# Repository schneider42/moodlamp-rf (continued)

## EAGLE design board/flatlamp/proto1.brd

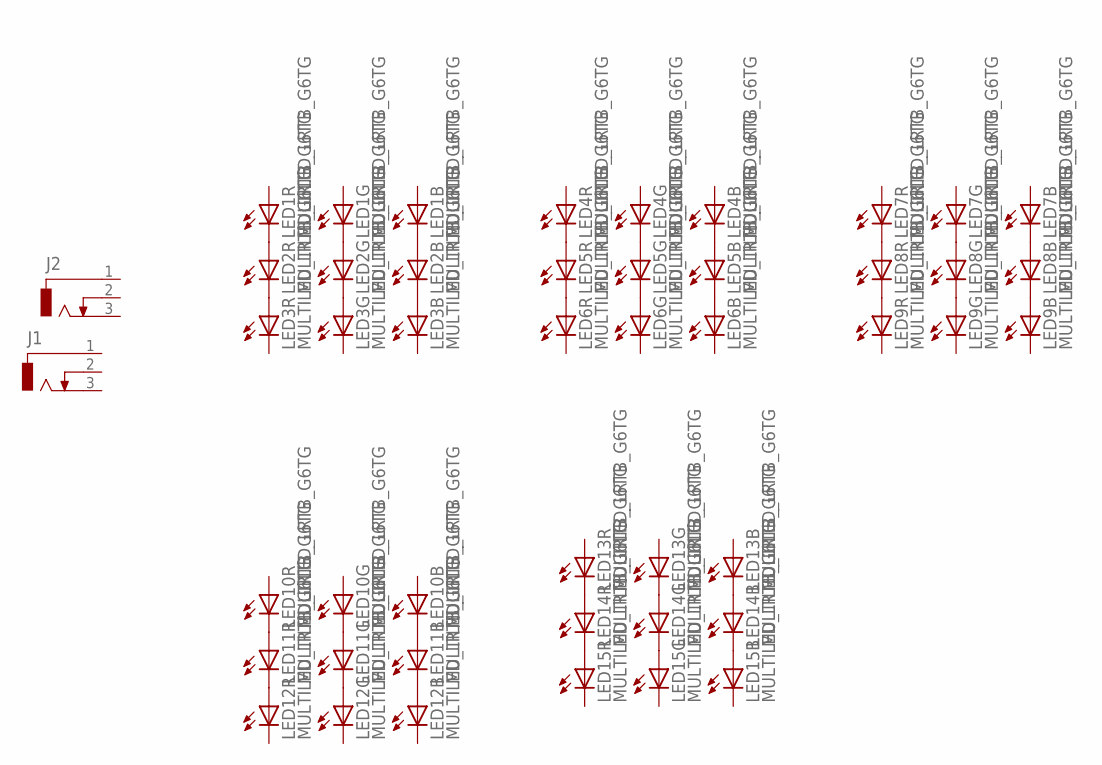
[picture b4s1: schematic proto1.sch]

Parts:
J1, J2: DCJ0303
LED1, LED2, LED3, LED4, LED5, LED6, LED7, LED8, LED9, LED10, LED11, LED12, LED13, LED14, LED15: MULTILED_LRTB_G6TG; P-LCC-6_TOPLED

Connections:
unnamed: LED1.C1 (C), LED2.A1 (A)
unnamed: LED1.C2 (C), LED2.A2 (A)
unnamed: LED1.C3 (C), LED2.A3 (A)
unnamed: LED2.C3 (C), LED3.A3 (A)
unnamed: LED2.C2 (C), LED3.A2 (A)
unnamed: LED2.C1 (C), LED3.A1 (A)
unnamed: LED4.C1 (C), LED5.A1 (A)
unnamed: LED4.C2 (C), LED5.A2 (A)
unnamed: LED4.C3 (C), LED5.A3 (A)
unnamed: LED5.C3 (C), LED6.A3 (A)
unnamed: LED5.C2 (C), LED6.A2 (A)
unnamed: LED5.C1 (C), LED6.A1 (A)
unnamed: LED7.C1 (C), LED8.A1 (A)
unnamed: LED7.C2 (C), LED8.A2 (A)
unnamed: LED7.C3 (C), LED8.A3 (A)
unnamed: LED8.C1 (C), LED9.A1 (A)
unnamed: LED8.C2 (C), LED9.A2 (A)
unnamed: LED8.C3 (C), LED9.A3 (A)
unnamed: LED11.C1 (C), LED12.A1 (A)
unnamed: LED10.C1 (C), LED11.A1 (A)
unnamed: LED10.C2 (C), LED11.A2 (A)
unnamed: LED11.C2 (C), LED12.A2 (A)
unnamed: LED10.C3 (C), LED11.A3 (A)
unnamed: LED11.C3 (C), LED12.A3 (A)
unnamed: LED13.C1 (C), LED14.A1 (A)
unnamed: LED13.C2 (C), LED14.A2 (A)
unnamed: LED13.C3 (C), LED14.A3 (A)
unnamed: LED14.C1 (C), LED15.A1 (A)
unnamed: LED14.C2 (C), LED15.A2 (A)
unnamed: LED14.C3 (C), LED15.A3 (A)

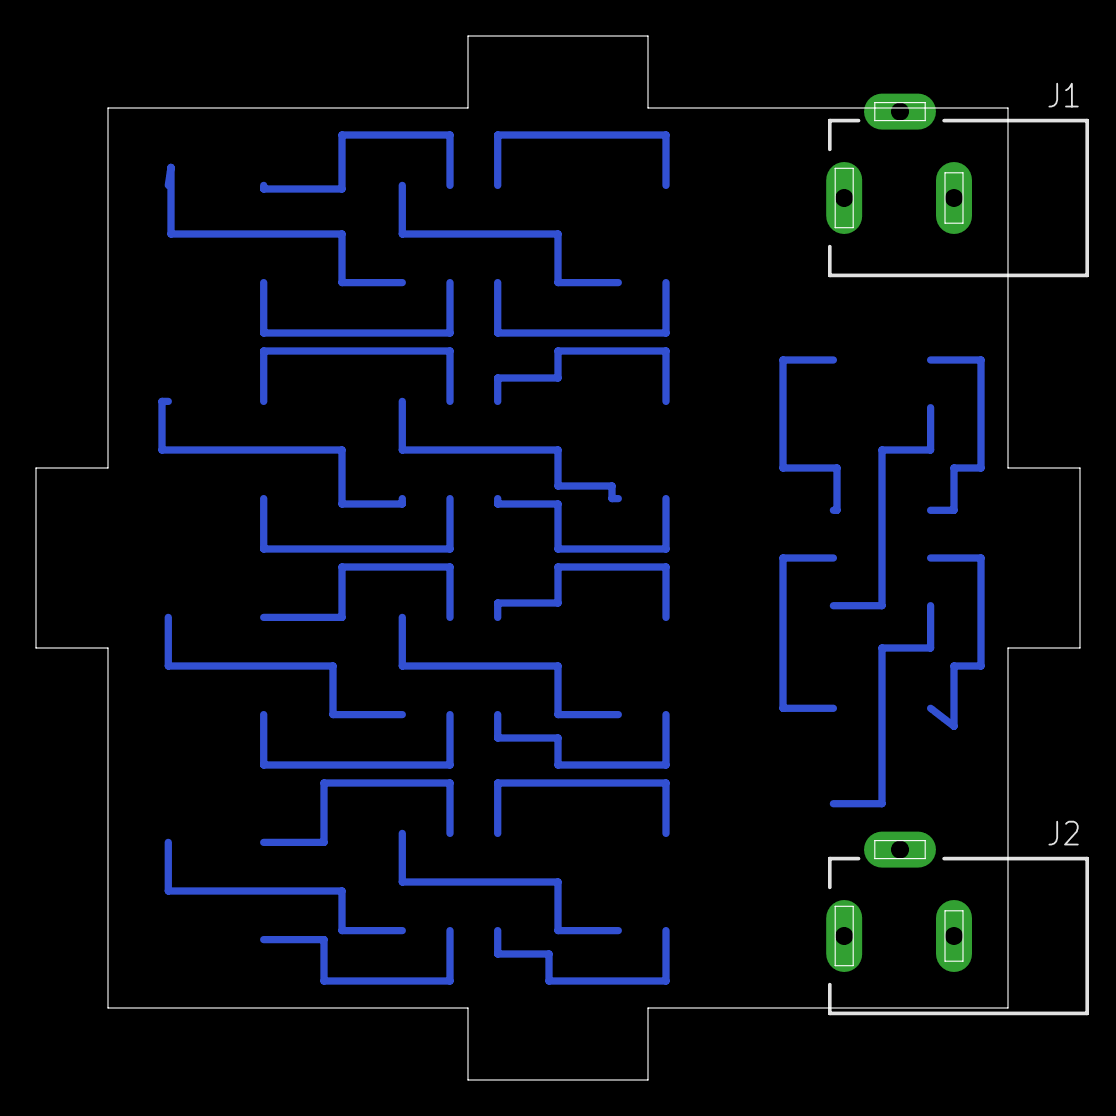
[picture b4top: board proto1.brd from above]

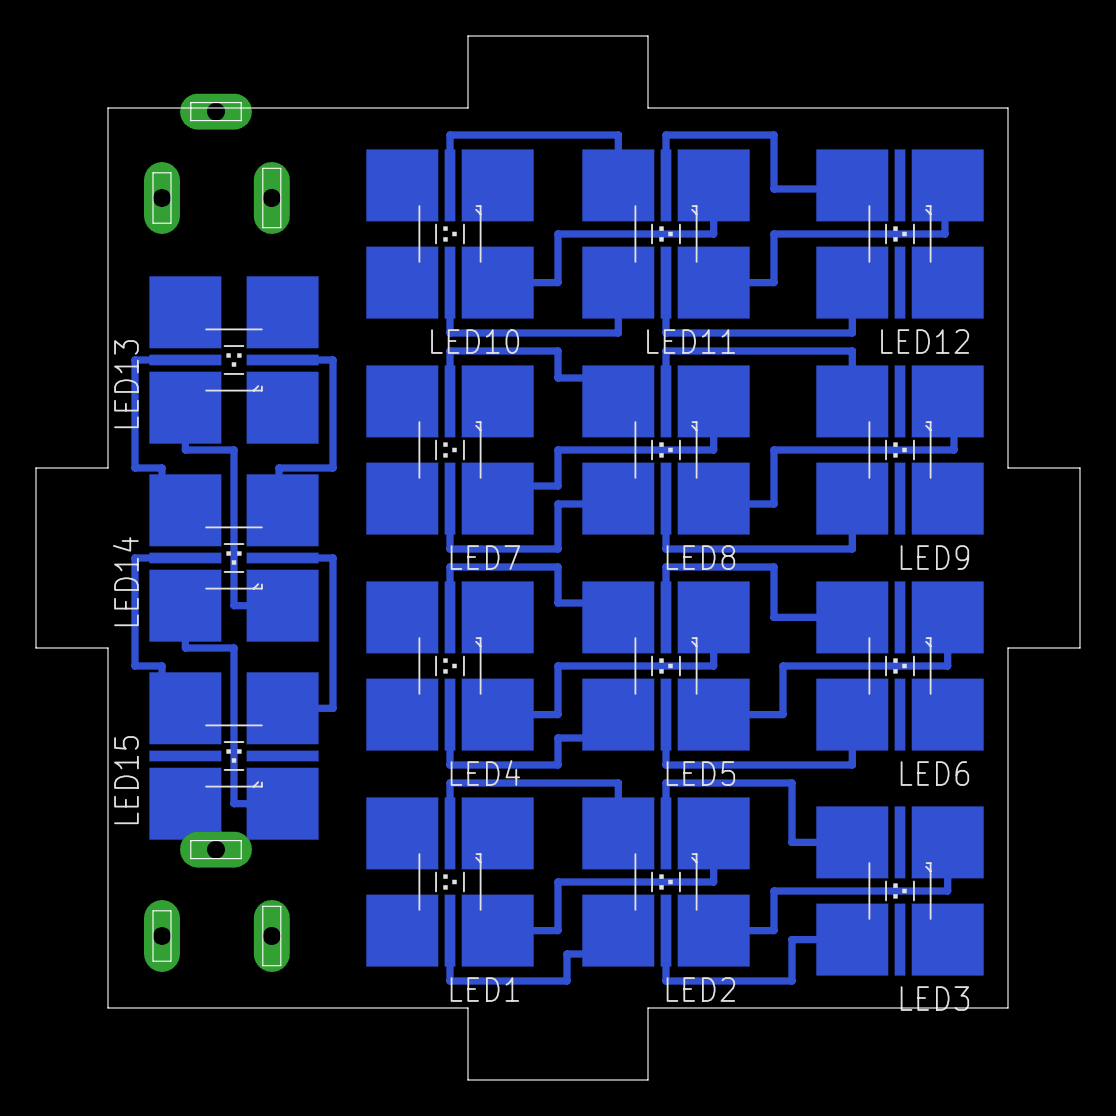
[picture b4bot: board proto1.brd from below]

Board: 2 copper layers, 58.0 x 58.0 mm, 17 parts (15 on the bottom side), 30 nets.

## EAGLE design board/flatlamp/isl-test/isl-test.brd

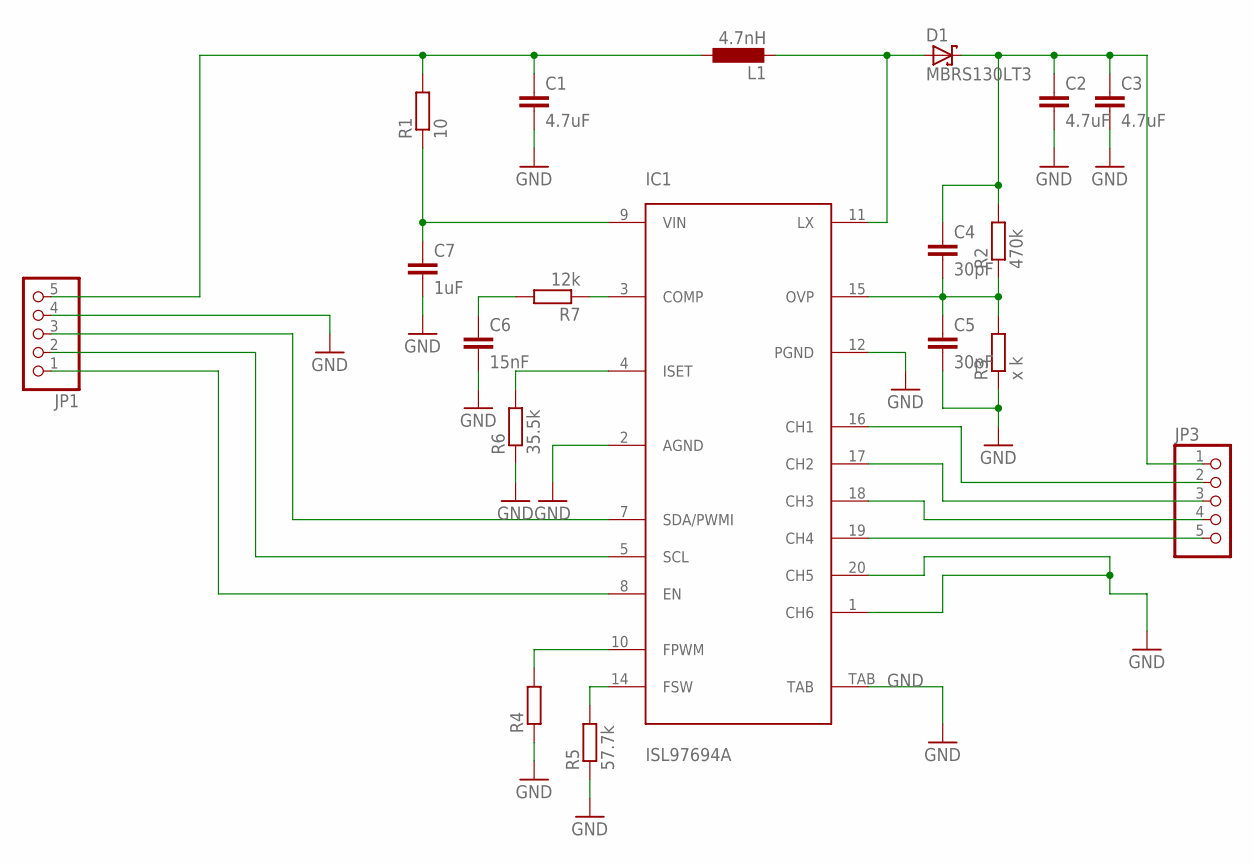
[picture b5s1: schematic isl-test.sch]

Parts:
C1, C2, C3: 4.7uF; C0805
C4, C5: 30pF; C0603
C6: 15nF; C0603
C7: 1uF; C0603
D1: MBRS130LT3; SMB
IC1: ISL97694A; TQFN-20
JP1, JP3: PINHD-1X5; 1X05
L1: 4.7nH; L1812
R1: 10; R0603
R2: 470k; R0603
R3: x k; R0603
R4: R-EU_R0603; R0603
R5: 57.7k; R0603
R6: 35.5k; R0603
R7: 12k; R0603

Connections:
GND: C1.2, C2.2, C3.2, C5.2, C6.2, C7.2, IC1.1 (CH6), IC1.2 (AGND), IC1.12 (PGND), IC1.20 (CH5), IC1.TAB, JP1.4, R3.1, R4.1, R5.1, R6.1
unnamed: C1.1, JP1.5, L1.1, R1.2
unnamed: D1.A, IC1.11 (LX), L1.2
unnamed: C4.2, C5.1, IC1.15 (OVP), R2.1, R3.2
unnamed: C2.1, C3.1, C4.1, D1.C, JP3.1, R2.2
unnamed: IC1.3 (COMP), R7.1
unnamed: C6.1, R7.2
unnamed: IC1.4 (ISET), R6.2
unnamed: IC1.10 (FPWM), R4.2
unnamed: IC1.14 (FSW), R5.2
unnamed: IC1.8 (EN), JP1.1
unnamed: IC1.5 (SCL), JP1.2
unnamed: IC1.7 (SDA/PWMI), JP1.3
unnamed: IC1.16 (CH1), JP3.2
unnamed: IC1.17 (CH2), JP3.3
unnamed: IC1.18 (CH3), JP3.4
unnamed: IC1.19 (CH4), JP3.5
VIN: C7.1, IC1.9 (VIN), R1.1

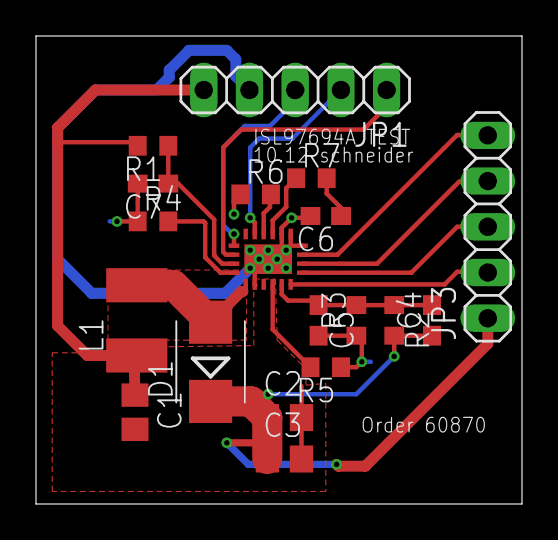
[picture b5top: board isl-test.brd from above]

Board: 2 copper layers, 27.0 x 26.0 mm, 19 parts (0 on the bottom side), 18 nets.

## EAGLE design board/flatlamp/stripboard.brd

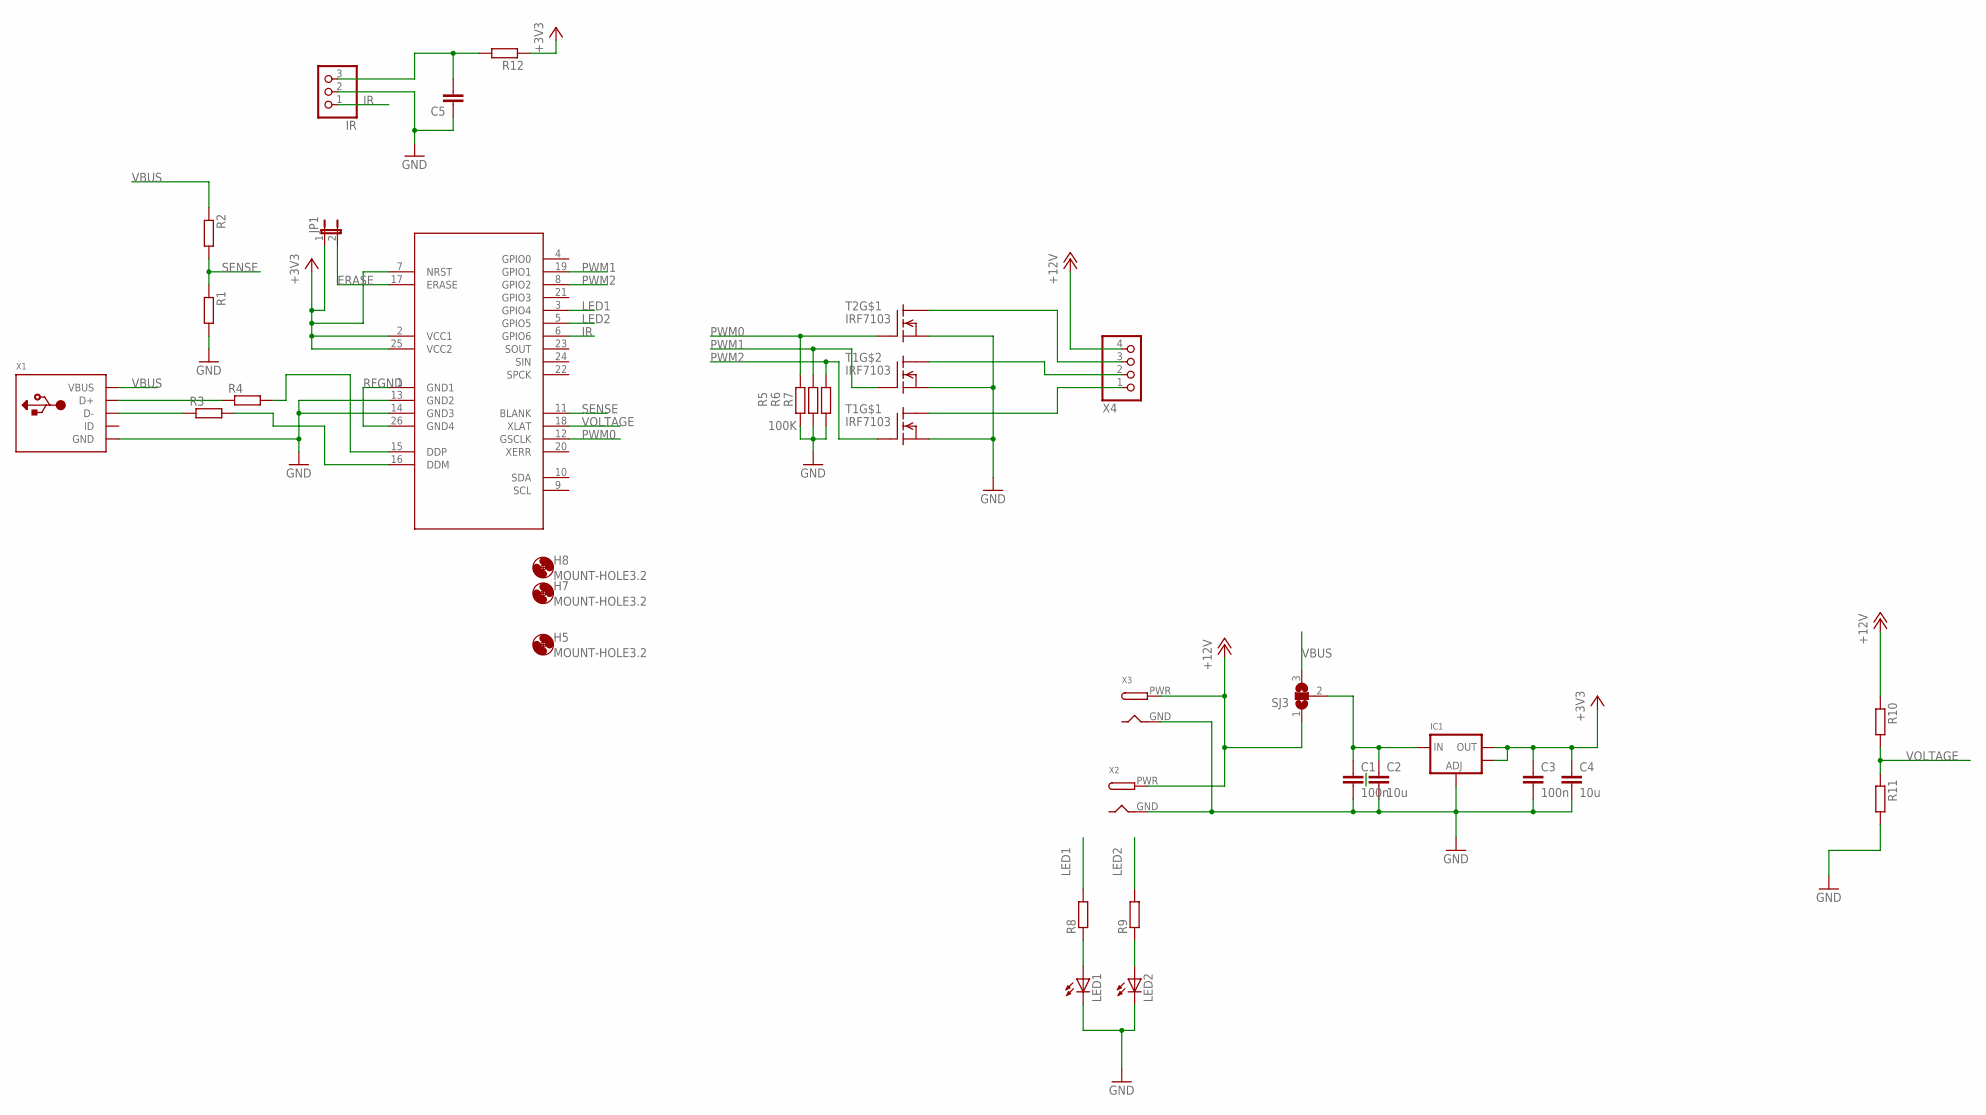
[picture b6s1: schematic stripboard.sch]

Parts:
C1, C3: 100n; C0805
C2, C4: 10u; C0805
C5: C-EUC0805; C0805
H5, H7, H8: MOUNT-HOLE3.2; 3,2
IC1: LM1117SOT223-REFLOW; SOT223-R
IR: PINHD-1X3; 1X03
JP1: JP1E; JP1
LED1, LED2: LEDCHIP-LED0805; CHIP-LED0805
R1, R2, R3, R4, R8, R9, R10, R11, R12: R-EU_R0805; R0805
R5, R6, R7: 100K; M0805
SJ3: SJ2W; SJ_2
T1, T2: IRF7103; SO-8
U$1: RFBOARD
X1: USBMINIB; USB-MINIB
X2, X3: DCBARRELPTH; DCJACK_2MM_PTH
X4: PINHD-1X4/90; 1X04/90

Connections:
+3V3: C3.1, C4.1, IC1.2 (OUT), IC1.4 (OUT1), JP1.1, R12.1, U$1.2 (VCC1), U$1.7 (NRST), U$1.25 (VCC2)
+12V: R10.1, SJ3.1, X2.PWR, X3.PWR, X4.4
ERASE: JP1.2, U$1.17 (ERASE)
GND: C1.2, C2.2, C3.2, C4.2, C5.1, IC1.1 (ADJ), IR.2, LED1.C, LED2.C, R1.2, R5.2, R6.2, R7.2, R11.2, T1.1 (S), T1.3 (S), T2.1 (S), U$1.13 (GND2), U$1.14 (GND3), X1.GND, X2.GND, X3.GND
IR: IR.1, U$1.6 (GPIO6)
LED1: R8.2, U$1.3 (GPIO4)
LED2: R9.2, U$1.5 (GPIO5)
unnamed: T1.8 (D1), X4.1
unnamed: T1.5 (D1), X4.2
unnamed: T2.8 (D1), X4.3
unnamed: LED1.A, R8.1
unnamed: LED2.A, R9.1
unnamed: R3.2, U$1.16 (DDM)
unnamed: R4.2, U$1.15 (DDP)
unnamed: R4.1, X1.D+
unnamed: C1.1, C2.1, IC1.3 (IN), SJ3.2
unnamed: R3.1, X1.D-
unnamed: C5.2, IR.3, R12.2
PWM0: R5.1, T2.2 (G), U$1.12 (GSCLK)
PWM1: R6.1, T1.4 (G), U$1.19 (GPIO1)
PWM2: R7.1, T1.2 (G), U$1.8 (GPIO2)
RFGND: U$1.1 (GND1), U$1.26 (GND4)
SENSE: R1.1, R2.2, U$1.11 (BLANK)
VBUS: R2.1, SJ3.3, X1.VBUS
VOLTAGE: R10.2, R11.1, U$1.18 (XLAT)

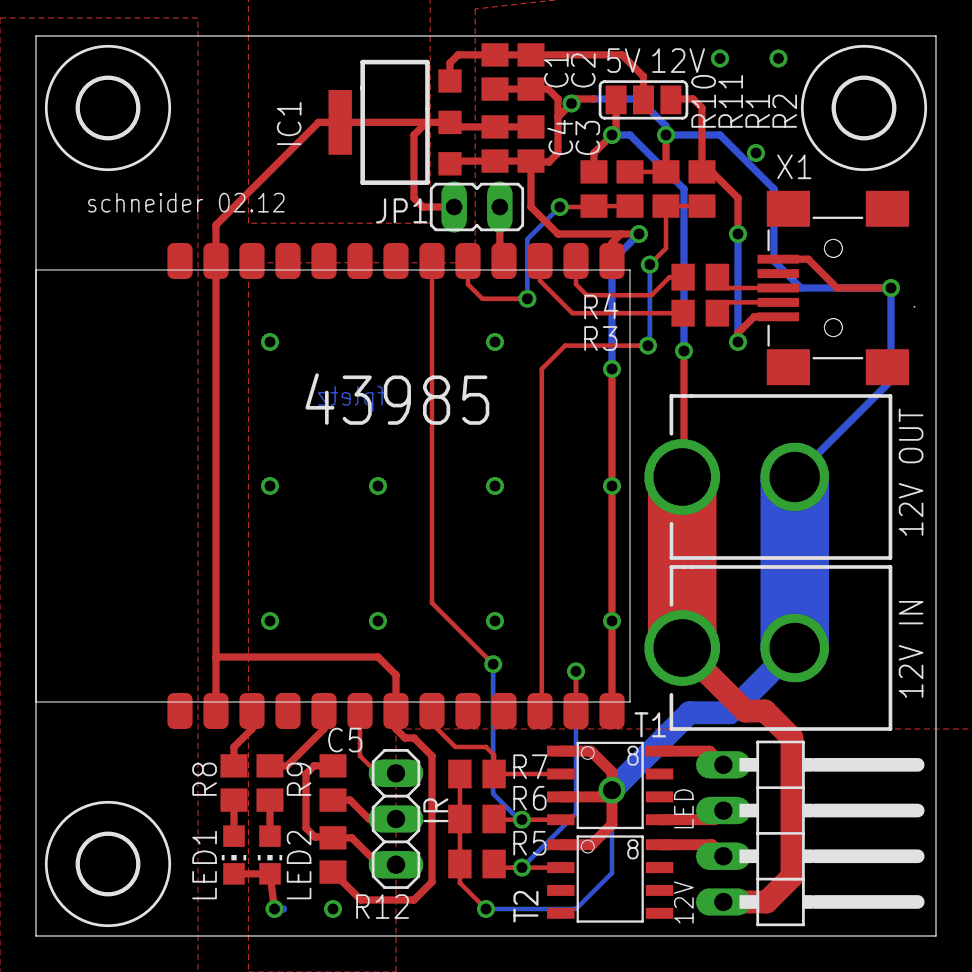
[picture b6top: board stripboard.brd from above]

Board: 2 copper layers, 50.0 x 50.0 mm, 33 parts (0 on the bottom side), 25 nets.

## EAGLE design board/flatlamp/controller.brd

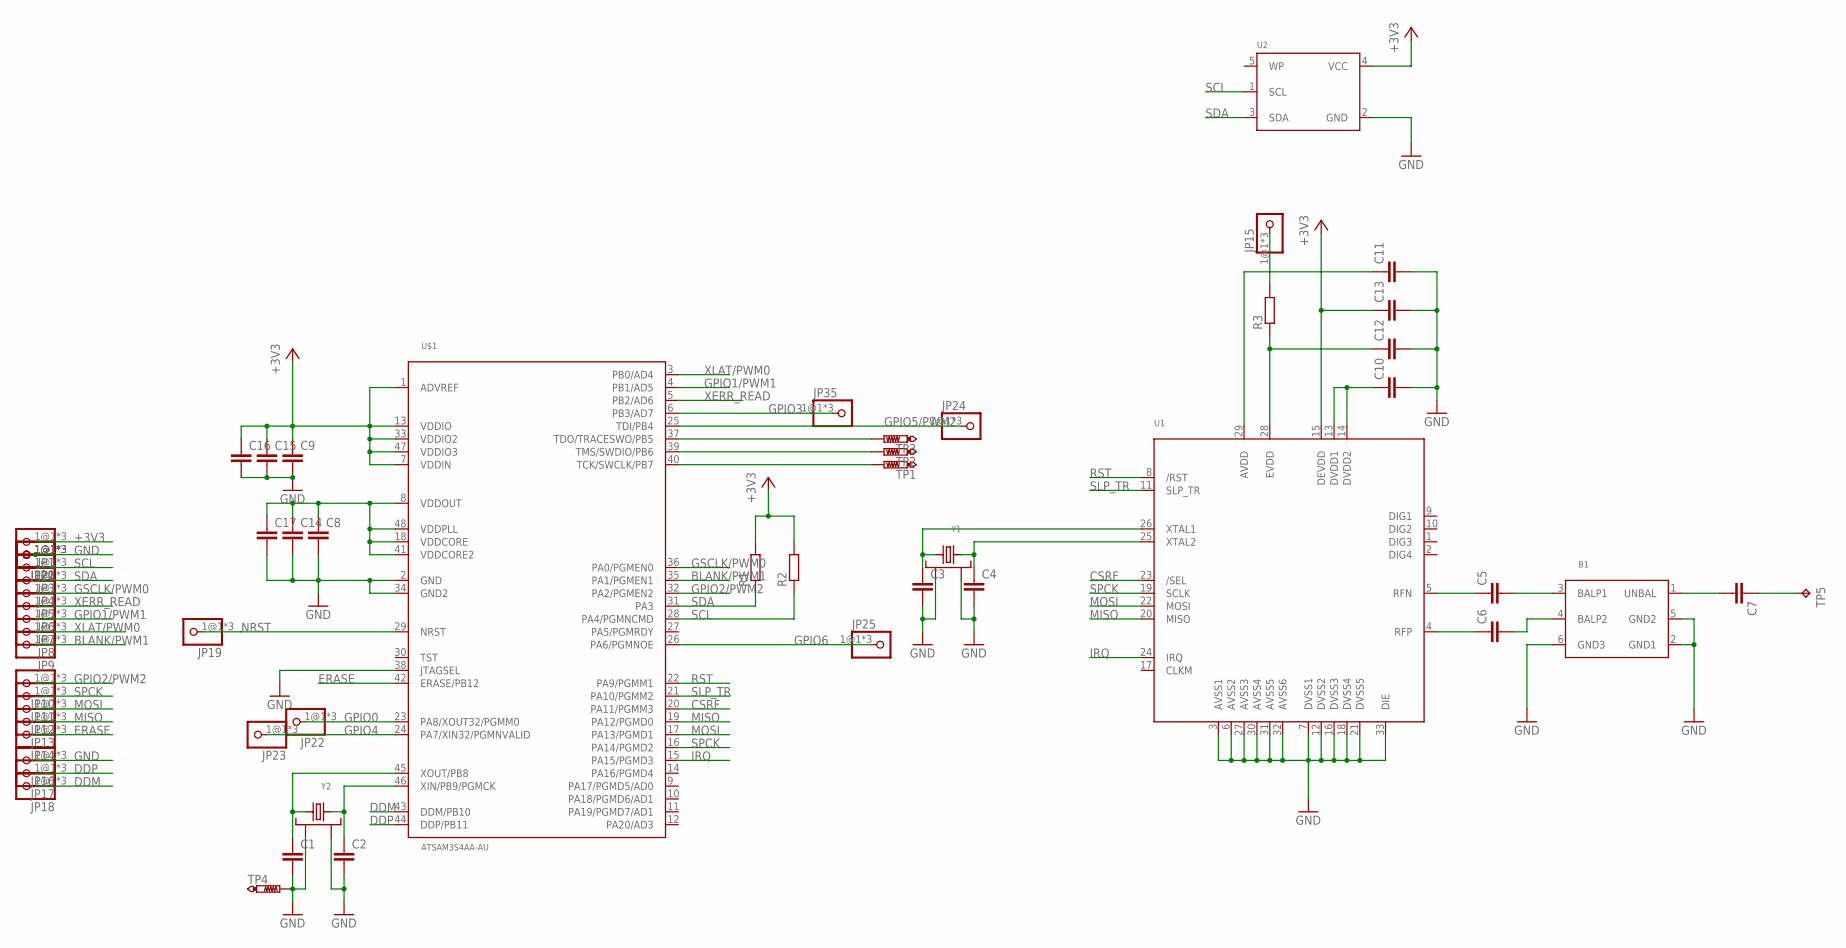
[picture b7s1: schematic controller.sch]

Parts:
B1: BALUN+LP; BALUN0805
C1, C2, C3, C4, C5, C6, C7: C-EUC0402K; C0402K
C8, C9, C10, C11, C12, C13, C14, C15, C16: C-EUC0603K; C0603K
C17: C-EUC0805K; C0805K
JP1, JP2, JP3, JP4, JP5, JP6, JP7, JP8, JP9, JP10, JP11, JP12, JP13, JP14, JP15, JP16, JP17, JP18, JP19, JP20, JP21, JP22, JP23, JP24, JP25, JP35: HEADER-1X1PAD; 1MMPAD
R1, R2: R-EU_R0402; R0402
R3: R-EU_R0805; R0805
TP1, TP2, TP3, TP4: PTR1TP15R; TP15R
TP5: TPTP15SQ; TP15SQ
U1: AT86RF212; 32QN2
U2: MCP24AA32; SOT23-5
U$1: ATSAM3S4AA-AU; LQFP48
Y1, Y2: CRYSTALTHIN; CRYSTAL_3.2X2.5

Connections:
+3V3: C9.1, C13.1, C15.1, C16.1, JP1.1@1, JP1.1@2, JP1.1@3, R1.2, R2.2, U1.15 (DEVDD), U2.4 (VCC), U$1.1 (ADVREF), U$1.7 (VDDIN), U$1.13 (VDDIO), U$1.33 (VDDIO2), U$1.47 (VDDIO3)
ANT: C7.1, TP5.TP
BLANK/PWM1: JP9.1@1, JP9.1@2, JP9.1@3, U$1.35 (PA1/PGMEN1)
CSRF: U1.23 (/SEL), U$1.20 (PA11/PGMM3)
DDM: JP18.1@1, JP18.1@2, JP18.1@3, U$1.43 (DDM/PB10)
DDP: JP17.1@1, JP17.1@2, JP17.1@3, U$1.44 (DDP/PB11)
ERASE: JP14.1@1, JP14.1@2, JP14.1@3, U$1.42 (ERASE/PB12)
GND: B1.2 (GND1), B1.5 (GND2), B1.6 (GND3), C1.2, C2.2, C3.2, C4.2, C8.2, C9.2, C10.2, C11.2, C12.2, C13.2, C14.2, C15.2, C16.2, C17.2, JP2.1@1, JP2.1@2, JP2.1@3, JP16.1@1, JP16.1@2, JP16.1@3, JP20.1@1, JP20.1@2, JP20.1@3, JP21.1@1, JP21.1@2, JP21.1@3, TP4.TP, U1.3 (AVSS1), U1.6 (AVSS2), U1.7 (DVSS1), U1.12 (DVSS2), U1.16 (DVSS3), U1.18 (DVSS4), U1.21 (DVSS5), U1.27 (AVSS3), U1.30 (AVSS4), U1.31 (AVSS5), U1.32 (AVSS6), U1.33 (DIE), U2.2 (GND), U$1.2 (GND), U$1.34 (GND2), U$1.38 (JTAGSEL), Y1.GND1, Y1.GND2, Y2.GND1, Y2.GND2
GPIO0: JP22.1@1, JP22.1@2, JP22.1@3, U$1.23 (PA8/XOUT32/PGMM0)
GPIO1/PWM1: JP7.1@1, JP7.1@2, JP7.1@3, U$1.4 (PB1/AD5)
GPIO2/PWM2: JP10.1@1, JP10.1@2, JP10.1@3, U$1.32 (PA2/PGMEN2)
GPIO3: JP35.1@1, JP35.1@2, JP35.1@3, U$1.6 (PB3/AD7)
GPIO4: JP23.1@1, JP23.1@2, JP23.1@3, U$1.24 (PA7/XIN32/PGMNVALID)
GPIO5/PWM2: JP24.1@1, JP24.1@2, JP24.1@3, U$1.25 (TDI/PB4)
GPIO6: JP25.1@1, JP25.1@2, JP25.1@3, U$1.26 (PA6/PGMNOE)
GSCLK/PWM0: JP5.1@1, JP5.1@2, JP5.1@3, U$1.36 (PA0/PGMEN0)
IRQ: U1.24 (IRQ), U$1.15 (PA15/PGMD3)
MISO: JP13.1@1, JP13.1@2, JP13.1@3, U1.20 (MISO), U$1.19 (PA12/PGMD0)
MOSI: JP12.1@1, JP12.1@2, JP12.1@3, U1.22 (MOSI), U$1.17 (PA13/PGMD1)
unnamed: C5.1, U1.5 (RFN)
unnamed: B1.3 (BALP1), C5.2
unnamed: C6.1, U1.4 (RFP)
unnamed: B1.4 (BALP2), C6.2
unnamed: C1.1, U$1.45 (XOUT/PB8), Y2.2
unnamed: C2.1, U$1.46 (XIN/PB9/PGMCK), Y2.1
unnamed: B1.1 (UNBAL), C7.2
unnamed: C3.1, U1.26 (XTAL1), Y1.2
unnamed: C4.1, U1.25 (XTAL2), Y1.1
unnamed: C12.1, R3.1, U1.28 (EVDD)
unnamed: C8.1, C14.1, C17.1, U$1.8 (VDDOUT), U$1.18 (VDDCORE), U$1.41 (VDDCORE2), U$1.48 (VDDPLL)
unnamed: C11.1, U1.29 (AVDD)
unnamed: JP15.1@1, JP15.1@2, JP15.1@3, R3.2
unnamed: C10.1, U1.13 (DVDD1), U1.14 (DVDD2)
unnamed: TP1.TP, U$1.40 (TCK/SWCLK/PB7)
unnamed: TP2.TP, U$1.39 (TMS/SWDIO/PB6)
unnamed: TP3.TP, U$1.37 (TDO/TRACESWO/PB5)
NRST: JP19.1@1, JP19.1@2, JP19.1@3, U$1.29 (NRST)
RST: U1.8 (/RST), U$1.22 (PA9/PGMM1)
SCL: JP3.1@1, JP3.1@2, JP3.1@3, R2.1, U2.1 (SCL), U$1.28 (PA4/PGMNCMD)
SDA: JP4.1@1, JP4.1@2, JP4.1@3, R1.1, U2.3 (SDA), U$1.31 (PA3)
SLP_TR: U1.11 (SLP_TR), U$1.21 (PA10/PGMM2)
SPCK: JP11.1@1, JP11.1@2, JP11.1@3, U1.19 (SCLK), U$1.16 (PA14/PGMD2)
XERR_READ: JP6.1@1, JP6.1@2, JP6.1@3, U$1.5 (PB2/AD6)
XLAT/PWM0: JP8.1@1, JP8.1@2, JP8.1@3, U$1.3 (PB0/AD4)

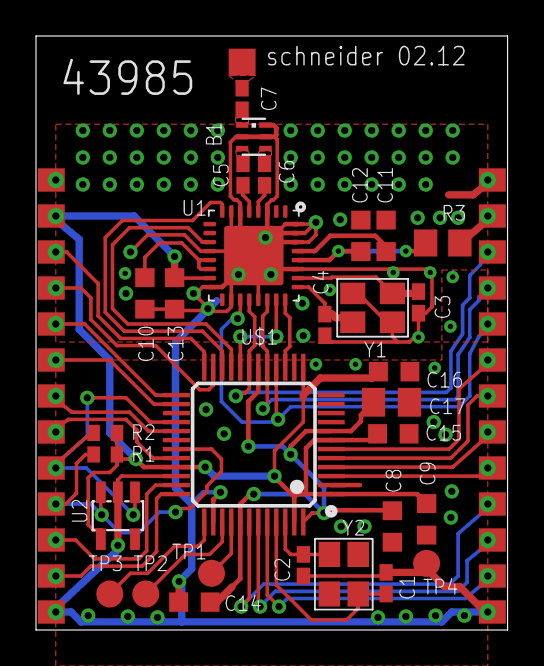
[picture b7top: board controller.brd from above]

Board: 2 copper layers, 26.2 x 33.0 mm, 57 parts (0 on the bottom side), 44 nets.

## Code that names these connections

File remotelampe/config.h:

/* vim:fdm=marker ts=4 et ai
 * {{{
 *         fnordlicht firmware next generation
 *
 *    for additional information please
 *    see http://koeln.ccc.de/prozesse/running/fnordlicht
 *
 * (c) by Alexander Neumann <alexander@bumpern.de>
 *     Lars Noschinski <lars@public.noschinski.de>
 *
 * This program is free software; you can redistribute it and/or modify
 * it under the terms of the GNU General Public License version 2 as
 * published by the Free Software Foundation.
 *
 * This program is distributed in the hope that it will be useful,
 * but WITHOUT ANY WARRANTY; without even the implied warranty of
 * MERCHANTABILITY or FITNESS FOR A PARTICULAR PURPOSE.  See the
 * GNU General Public License for more details.
 *
 * You should have received a copy of the GNU General Public License
 * along with this program; if not, write to the Free Software
 * Foundation, Inc., 675 Mass Ave, Cambridge, MA 02139, USA.
 *
 * For more information on the GPL, please go to:
 * http://www.gnu.org/copyleft/gpl.html
 }}} */

#ifndef _FNORDLICHT_CONFIG_H
#define _FNORDLICHT_CONFIG_H

#define BOARD_0_1       0       //old moodlamp design
#define BOARD_RF_0_1    1       //proto rf board
#define BOARD_RF_0_2    2       //current rf board

#ifndef BOARD
#define BOARD   BOARD_RF_0_2
#endif

#ifndef F_CPU
    #define F_CPU 18432000UL
#endif

#ifndef LED_PORT
#define LED_PORT PORTA
#endif

#ifndef LED_PORT_DDR
#define LED_PORT_DDR DDRA
#endif

#ifndef LED_PORT_INVERT
#define LED_PORT_INVERT 0
#endif

/* color <-> channel assignment */
#define CHANNEL_RED     0
#define CHANNEL_GREEN   1
#define CHANNEL_BLUE    2

#define RC5_DECODER 1
#define RS485_CTRL  1
#define SCRIPT_SPEED_CONTROL 1
#define STATIC_SCRIPTS 1
#define USB_CTRL 1
#define UART_BAUDRATE 230400
#define SERIAL_UART 1

#define CONFIG1_PIN     PB0
#define CONFIG1_PORT     B

#define JUMPER1C1_PIN     PC3
#define JUMPER1C1_PORT    C

#define JUMPER1C2_PIN     PC3
#define JUMPER1C2_PORT    C

#define LED3_PIN     PA4
#define LED3_PORT    A

#define LED2_PIN     PA5
#define LED2_PORT    A

#define LED1_PIN     PA7
#define LED1_PORT    A

#define xRC5C2_PORT     PORTB
#define	xRC5C2_IN       PINB
#define	xRC5C2          PB1			// IR input low active

#define xRC5C1_PORT     PORTD
#define	xRC5C1_IN       PIND
#define	xRC5C1          PD6			// IR input low active

#define ADC_MINBATIDLE  530         //4v

/* debug defines */
#ifndef DEBUG
#define DEBUG 0
#endif

/* include the script intpreter per default */
#ifndef STATIC_SCRIPTS
#define STATIC_SCRIPTS 1
#endif

/* include uart support per default */
#ifndef SERIAL_UART
#define SERIAL_UART 0
#endif

/* disable at keyboard decoder per default (EXPERIMENTAL) */
/* ATTENTION: THIS IS EXPERIMENTAL AND DOES NOT WORK ATM! */
#ifndef AT_KEYBOARD
#define AT_KEYBOARD 0
#endif

/* disable rc5-decoder per default */
#ifndef RC5_DECODER
#define RC5_DECODER 1
#endif

/* disable scripts speed control per default */
#ifndef SCRIPT_SPEED_CONTROL
#define SCRIPT_SPEED_CONTROL 1
#endif

/* fifo size must be a power of 2 and below 128 */
//#define UART_FIFO_SIZE 32
#ifndef UART_BAUDRATE
#define UART_BAUDRATE 19200
#endif

#ifndef PWM_USESCALE
#define PWM_USESCALE
#endif

/* enable this if you want to control a fnordlicht via RS485 */
#if RS485_CTRL

#define TEENSY_SUPPORT

#define RS485_TX_PIN_PORT   C
#define RS485_TX_PIN_PIN    PC4

#define RS485_NRX_PIN_PORT  C
#define RS485_NRX_PIN_PIN   PC5

#define ZBUS_BAUDRATE 115200
/*#define RS485_TX_DDR    DDRD
#define RS485_RX_DDR    DDRD
#define RS485_RX_PORT   PORTD
#define RS485_TX_PORT   PORTD

#define RS485_TX_PIN    PD4
#define RS485_NRX_PIN   PD5*/

#endif

/*#if (RS485_CTRL == 1) && (SERIAL_UART == 1) && !(ROLE == ROLE_MASTER)
#error "RS485_CTRL and SERIAL_UART are mutually exclusive!"
#endif*/


#include <avr/version.h>

/* check for avr-libc version */
#if __AVR_LIBC_VERSION__ < 10604UL
#error newer libc version (>= 1.6.4) needed!
#endif

/* check if cpu speed is defined */
#ifndef F_CPU
#error please define F_CPU!
#endif

/* check if this cpu is supported */
#if !(defined(__AVR_ATmega8__) || defined(__AVR_ATmega88__) || defined(__AVR_ATmega168__) || defined(__AVR_ATmega16__) || defined(__AVR_ATmega324P__)  || defined(__AVR_ATmega644P__) || defined(__AVR_ATmega32__))
#error "this cpu isn't supported yet!"
#endif

/* cpu specific configuration registers */
#if defined(__AVR_ATmega8__)
/* {{{ */
#define _ATMEGA8

#define _TIMSK_TIMER1 TIMSK
#define _UCSRB_UART0 UCSRB
#define _UDRIE_UART0 UDRIE
#define _TXEN_UART0 TXEN
#define _RXEN_UART0 RXEN
#define _RXCIE_UART0 RXCIE
#define _UBRRH_UART0 UBRRH
#define _UBRRL_UART0 UBRRL
#define _UCSRC_UART0 UCSRC
#define _UCSZ0_UART0 UCSZ0
#define _UCSZ1_UART0 UCSZ1
#define _SIG_UART_RECV_UART0 SIG_UART_RECV
#define _SIG_UART_DATA_UART0 SIG_UART_DATA
#define _UDR_UART0 UDR
#define UCSR0A UCSRA
#define UCSR0C UCSRC
#define MPCM0 MPCM
#define UCSZ00 UCSZ0
#define UCSZ01 UCSZ1
#define UCSZ02 UCSZ2
#define UBRR0H UBRRH
#define UBRR0L UBRRL
#define UCSR0B UCSRB
#define RXEN0 RXEN
#define TXEN0 TXEN
#define RXC0 RXC
#define RXB80 RXB8
#define UDR0 UDR

/* }}} */
#elif defined(__AVR_ATmega16__) || defined(__AVR_ATmega32__)
/* {{{ */
#define _ATMEGA16

#define _EICRA MCUCR
#define _EIMSK GICR
#define _TIMSK_TIMER1 TIMSK
#define _UCSRB_UART0 UCSRB
#define _UDRIE_UART0 UDRIE
#define _TXEN_UART0 TXEN
#define _RXEN_UART0 RXEN
#define _RXCIE_UART0 RXCIE
#define _UBRRH_UART0 UBRRH
#define _UBRRL_UART0 UBRRL
#define _UCSRC_UART0 UCSRC
#define _UCSZ0_UART0 UCSZ0
#define _UCSZ1_UART0 UCSZ1
#define _SIG_UART_RECV_UART0 SIG_UART_RECV
#define _SIG_UART_DATA_UART0 SIG_UART_DATA
#define _UDR_UART0 UDR
#define UCSR0A UCSRA
#define UCSR0C UCSRC
#define MPCM0 MPCM
#define UCSZ00 UCSZ0
#define UCSZ01 UCSZ1
#define UCSZ02 UCSZ2
#define UBRR0H UBRRH
#define UBRR0L UBRRL
#define UCSR0B UCSRB
#define RXEN0 RXEN
#define TXEN0 TXEN
#define RXC0 RXC
#define RXB80 RXB8
#define UDR0 UDR

/* }}} */

#elif defined(__AVR_ATmega88__) || defined(__AVR_ATmega168__)|| defined(__AVR_ATmega324P__) || defined(__AVR_ATmega644P__)
/* {{{ */
#define _ATMEGA88
#define _EICRA EICRA
#define _EIMSK EIMSK
#define _TIMSK_TIMER1 TIMSK1
#define _UCSRB_UART0 UCSR0B
#define _UDRIE_UART0 UDRIE0
#define _TXEN_UART0 TXEN0
#define _RXEN_UART0 RXEN0
#define _RXCIE_UART0 RXCIE0
#define _UBRRH_UART0 UBRR0H
#define _UBRRL_UART0 UBRR0L
#define _UCSRC_UART0 UCSR0C
#define _UCSZ0_UART0 UCSZ00
#define _UCSZ1_UART0 UCSZ01
#define _SIG_UART_RECV_UART0 SIG_USART_RECV
#define _SIG_UART_DATA_UART0 SIG_USART_DATA
#define _UDR_UART0 UDR0
/* }}} */
#endif


#endif /* _FNORDLICHT_CONFIG_H */

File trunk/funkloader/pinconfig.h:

/*
 * Copyright(C) 2008 Stefan Siegl <stesie@brokenpipe.de>
 *
 * This program is free software; you can redistribute it and/or modify
 * it under the terms of the GNU General Public License as published by
 * the Free Software Foundation; either version 3 of the License, or
 * (at your option) any later version.
 *
 * This program is distributed in the hope that it will be useful,
 * but WITHOUT ANY WARRANTY; without even the implied warranty of
 * MERCHANTABILITY or FITNESS FOR A PARTICULAR PURPOSE.  See the
 * GNU General Public License for more details.
 *
 * You should have received a copy of the GNU General Public License
 * along with this program; if not, write to the Free Software Foundation,
 * Inc., 51 Franklin Street, Fifth Floor, Boston, MA 02110-1301  USA
 */

#ifndef PINCONFIG_H
#define PINCONFIG_H

#define SPI_CS_RFM12_PORT PORTB
#define SPI_CS_RFM12_DDR  DDRB
#define SPI_CS_RFM12      PB4

#define SPI_DDR           DDRB
#define SPI_MOSI          PB5
#define SPI_MISO          PB6
#define SPI_SCK           PB7

#define INT_PORT          PIND
#define INT_PIN           PD2

#define baud 19200
/* If you don't want to have status LEDs, simply comment out these */
#define STATUS_LED_PORT   PORTA
#define STATUS_LED_DDR    DDRA
#define STATUS_LED_TX     PA0
#define STATUS_LED_RX     PA1



#endif

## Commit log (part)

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2008-11-25 Added tag dir for mld/moodlamp-rf
2008-11-25 Removed some debug output
2008-11-28 Added colored placement
2008-11-28 Imprted new colored placements
2008-11-28 Added serial bootloader
2008-11-28 rm swp
2008-11-28 Added new remote and bigger serial buffer for zbusloader
2008-11-28 Various fixes ;)
2008-11-29 Added zbusloader for bootloading via rs485
2008-11-29 removed git files
2008-12-21 Use new zbus Init full 256 entries in the routing table Added new fade cmd Added new auto config cmd
2008-12-21 refactored zbusloader
2008-12-21 updated mld
2008-12-21 Added dreic scripts
2008-12-21 Added fuses
2008-12-21 Fixed fade issue
2008-12-22 Added first dreic source
2008-12-22 Deletet vim swap
2008-12-22 Removed debug output
2008-12-22 Added pwm table tools
2008-12-22 Added script dir for dreic testing
2008-12-22 Script updates
2008-12-22 Added serialsniff
2008-12-22 Added moodlamp bases rs485 sniffer
2008-12-22 Added skript so continously flash lamps on the bus
2008-12-22 Moved the dreic scripts
2008-12-27 Added scripts for 25c3
2009-02-01 dreic bridge used at 25c3
2009-02-01 Removed some flicker
2009-02-01 Improved zbus handling
2009-02-01 Commented watchdog for 25c3
2009-02-01 updated stress fade
2009-02-01 print more human
2009-02-01 fast blinking stress script
2009-02-01 Added quote from hope
2009-02-01 fixed set color
2009-02-13 Cleanup of serial handler
2009-02-13 Cleanup of cache
2009-02-13 Added pinutils from ethersex
2009-02-13 Added comments to makefile
2009-02-13 cleanup
2009-02-13 Moved rf disable into interfaces.c
2009-02-14 new plugins: ambilight mplayer video filter and sound beatz moodblinker
2009-03-03 Added simple gui for the muc setup
2009-03-03 Added broadcast
2009-03-24 MOved to newer avr libc
2009-03-24 And back..
2009-03-24 blubb
2009-03-24 eeprom fuckup
2009-03-25 Changed symbol to ATMega644P. Removed IRQ solder jumper
2009-03-27 Stromversorgung zeigt nach unten und nichtmehr zum ISP-Stecker. Vierpoliger Busverbinder incl. Stromversorgung. Zusaetzliche Kondensatoren zur Stabilisierung. Drei zusaetzliche Status-LEDs Ein Analog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
2009-03-30 Drei digitale Ausgaenge.
2009-03-30 Moved C1 on top
2009-04-05 mld housecleaning ;)
2009-04-05 argv mods & cleanups (indent :P)
2009-04-19 V0.3 of board
2009-04-19 Tagged board 0.3
2009-04-19 Added #!
2009-06-30 Added detection of hardware revision
2009-06-30 Use different pins with rc5
2009-06-30 Added new zbus. buggy :(
2009-06-30 Updated random script with slower speed
2009-06-30 Added hardware revision to version cmd
2009-06-30 Added adc routines
2009-07-01 moved config to global read adc at start and when broadcasting blink red when vcc < 4v
2009-07-01 Switch on the auxiliary leds
2009-07-01 Read hardware revision Read adc value
2009-07-03 Moved states to control.h
2009-07-03 added new stress script
2009-07-03 Shutdown at 4.0V
2009-07-03 Enter power down after detecting low battery. A lamp with usb, rf and rs485 drwas about 4mA when in power down.
2009-07-04 Removed state variable for low bat in main loop
2009-07-04 moved call to update_pwm_timeslots to where it originaly belonged
2009-07-05 Inserted all values
2009-07-05 Removed wrong sch.png, top.png, parts
2009-07-05 Added bom and media files for board 0.21
2009-07-05 bom for 0.3
2009-07-05 removed parts file
2009-07-05 Added bom file
2009-07-05 Inserted 0H for the coil Updated bom Added grouped bom
2009-07-05 Added readme
2009-07-05 Updated bom Added README
2009-07-05 removed old bot and top layers
2009-07-05 Added rx and tx led for rf and usb
2009-07-05 Added link to smd soldering
2009-07-05 Added media files for 0.3
2009-07-05 removed 0.3 tag
2009-07-05 Added 0.3 board with media files
2009-07-05 Added schematic in png and pdf for 0.21
2009-07-05 Added brd in pdf and png for 0.21
2009-07-05 speak english or die
2009-07-05 moved ihexfile and moodlamp stuff into own modules
2009-07-08 Moved client code into mldclient. cleaned up imports
2009-07-13 MAX487, AKL166-4, RFM12
2009-07-13 retagged
2009-07-13 retagged board
2009-08-02 disabled lowbat detection
2009-08-11 added adresses
2009-08-11 moved
2009-08-11 Added front+back per c
2009-08-27 added some bus aware scripts
2009-08-30 added uberbus branch
2009-08-30 removed zbus
2009-08-30 removed dreic stuff
2009-09-03 Added binary release
2009-09-03 namespace fix
2009-09-03 fix power regression
2009-09-03 added delay for version
2009-09-03 correct ir pin for 0.21
2009-09-03 remove fnordlicht.eep
2009-09-03 new hex
2009-09-05 new ip
2009-09-17 0 für alle Moodlamps auch bei 014
2009-09-18 added tcom branch
2009-09-22 added telblinker
2009-10-28 added contents of the set
2009-10-29 set-content update
2009-10-29 added qr code
2009-11-12 some compiler options
2009-11-12 updated ip
2009-11-12 moved colorgui added blink.py
2009-11-12 code clearup
2009-11-25 teamtecom in its first version
2009-11-25 modifications for the bootloader added moodlistener
2009-11-27 added wave and fade
2009-11-28 police wave
2010-01-06 added kitchen wave!
2010-01-07 added lampmap added wave4
2010-01-09 added msfade branch
2010-01-10 remove glitch when channel is at 255
2010-01-10 removed test comments
2010-01-10 added alternative fading
2010-01-10 added fadems and fademsalt
2010-01-10 removed obsolete file
2010-01-10 added speed settings to makefile removed avrdude port
2010-01-10 removed obsolete fifos
2010-01-10 removed old code
2010-01-10 added wdt timer
2010-01-10 disable zbus tx....
2010-01-15 added remotelamp source
2010-02-14 "corrected ml-rf.pdf, it was printed in mirror view
2010-02-15 +aligned telnet output due to python string formatting +reset all moodlamps with "moodlamp id" = 0 for all moodlamps, synchronizes moodlamps +modified ? message
2010-02-16 mld: code cleanup (removed tabs, indentation) +extended help message with hidden features
2010-02-16 mld: adjusted <prog Nr> of command 014 [moodlamp_id] <prog Nr> to ir-remote prog Numbers
2010-02-19 mld: added gpl licence headers and file
2010-02-22 infected mld/scripts with gpl
2010-02-22 Schematic-changes: added license information. Creative Commons: CC-BY-SA 3.0 DE Attribution and Share Alike http://creativecommons.org/licenses/by-sa/3.0/de/
    Changes in trunk 0.3 schematic only:
    removed unused wires where C12 placed in 0.21
    Renewed ml-rf.pdf, sch.png (300dpi)
    in tag 0.2 and 0.21 and trunk (retag 0.3 later)
2010-02-23 deleted 0.3 tag
2010-02-23 retaged board 0.3 from trunk
2010-03-15 updated heat shrink diameter
2010-03-31 updated speeds
2010-04-07 update set content Kit Revision 4: new colorcodes, new ir receiver
    we should make different set-content files or some other file
    for every kit revision.
2010-04-20 aded buslamp
2010-04-25 adde bus firmware
2010-04-25 address = 0x55
2010-05-06 write eeprom when flashing
2010-05-08 mldclient.py update from DaN
    use of name instead of id works (again?).
    id = 0 for "004 - toggle pause" implemented like advertised in help
    "014 - run program" works now like the ir remote (same range and numbers)
2010-06-28 acab scripts
2010-06-28 adde crcmod archive
2010-06-29 buslamp code
2010-06-29 ubloader code
2010-07-09 added simple bridge
2010-07-13 Changes in mld scripts: -added colorui.py with telnet interface for mld$ -address lamps with strings not only numbers$ -added debug and usage getopt options$ -added logging$ -replaced print with logg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
2010-07-13 new directory for flash and wahl scripts
2010-07-13 renamed blink to blink.sh
2010-07-13 ooops, wrong dir for blink.py
2010-07-16 added busaufbau
2010-10-19 code cleanup with pylint use python logging module remove unused modules modified daemon fork use python getopt, +usage, +port, +... options
2010-10-22 +blink_w-advanced.py +examples
2010-10-26 Starting experimental branch - new features: command for firmware-side fading in mld; needed firmware changes
2010-10-27 new feature: "fadems" command for firmware-side fading to mld and changes to moodlamp-rf firmware for fadems to actually work
2010-11-02 moved settings from mld.py to conf.py
2010-11-10 fixed: Instance of 'ReadSerial' has no 'stop' member "r" reset command works now
2010-11-10 used conf.py to fix #TODO ttyUSB0 hardcoded +added config var for baudrate
2010-11-21 removed print commands and replaced them with logging nicer output
2010-12-24 added row test fixed issue with escape sequencing
2010-12-24 script to test single lamp
2010-12-24 blink read hex ids error in fadems
2011-04-21 updated kit revision
2012-01-19 buslamp: reworked schematic
2012-01-19 added bridge layout
2012-12-16 read id in uberbus format
2012-12-16 added 16 Bit 288 Hz PWM
2012-12-16 added buffered commands and probabilistic reset command
2012-12-16 added bridge firmware from 28c3
2012-12-16 removed old svn files
2012-12-16 added some old scripts
2012-12-16 new bom print commands
2012-12-16 new boards
2012-12-16 table scripts
2012-12-16 rocket blink script
2012-12-16 new reset commands
2012-12-16 avrdude: ignore chip id
2012-12-16 new set contents
2013-03-20 moodlamp-bus: build .bin by default
2013-03-20 moodlamp-bus: renamed makefile
2013-03-21 ubloader: flash binary files by default
2013-05-17 made the stuff compile again with the new avr-libc
2013-05-17 slower standard fade
2013-05-17 compiled new firmware image
2013-05-17 acab: removed crcmod dependency
2013-05-17 acab: updated to new synchonization protocol
2013-05-17 added probabilistic reset command for acab lamps
2013-05-17 acab: added test script to scan the address space
2013-05-17 update of the ubloader/rs485bridge stuff
2013-07-03 Added extra escaping to make lamp 5C (ASCII: \ work)
2013-07-03 Changed makefile standard for moodlamp-bus to m324p
2013-07-03 unified the address handling
2013-07-03 added helper scripts for acab
2014-10-29 feat(board): Second revision of the buslamp board
2015-05-14 doc(kit-v4): add contents of kit v4
2015-05-14 doc(kit-v4): update contents of kit v4
2015-05-14 doc(kit-v4): move file into board dir
2015-05-14 doc(kit-v4): Make stuff a code block
2015-05-14 doc(kit-v4): Make it a github mark down
2015-05-19 ATmega324A with RS485 fix
2015-12-11 feat(board): Buslamp r4 design
